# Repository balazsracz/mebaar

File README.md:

# Readme

This repository contains designs and files I made and collected for the Modelleisenbahn-Club Baar.

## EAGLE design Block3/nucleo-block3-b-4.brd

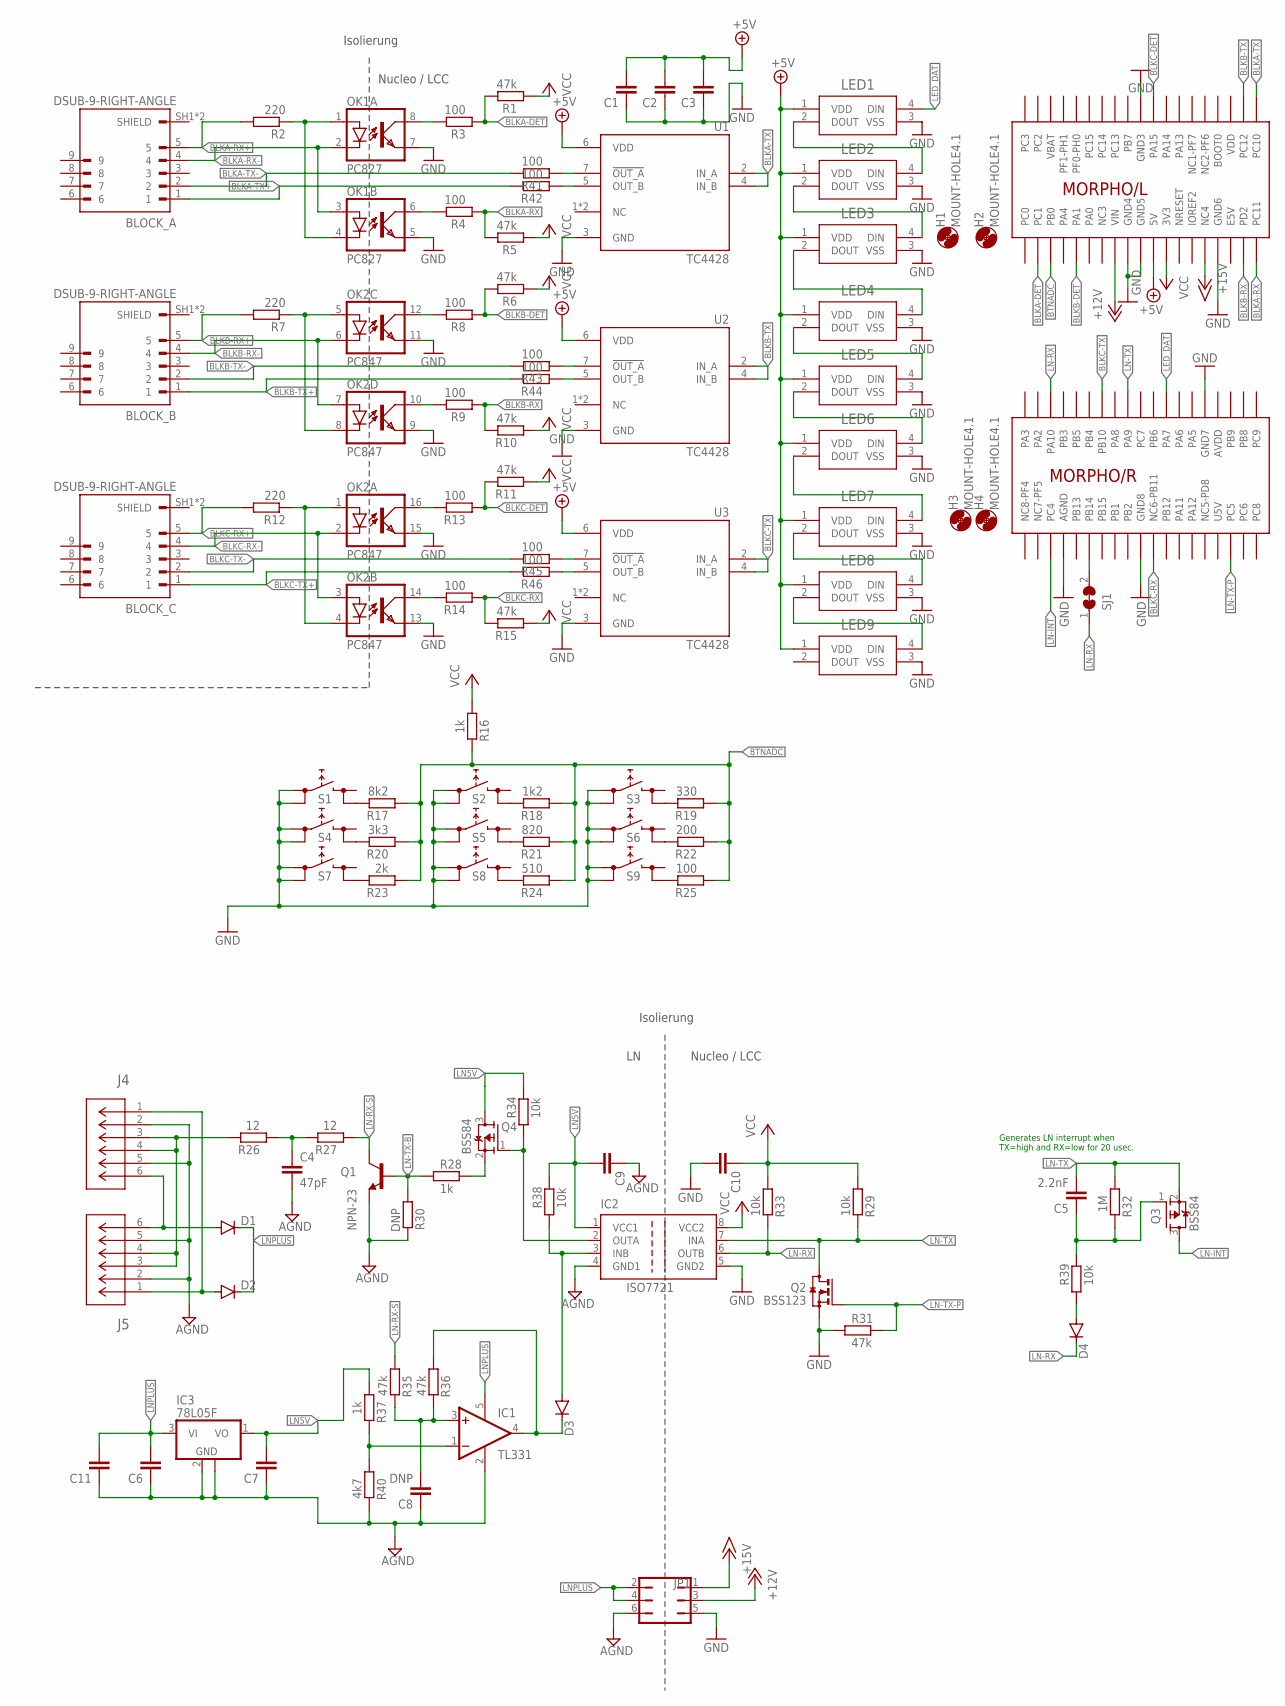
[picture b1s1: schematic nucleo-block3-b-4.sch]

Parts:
BLOCK_A: DSUB-9-RIGHT-ANGLE; ASSMANN_A-DS_09_A_KG-T2S
BLOCK_B: DSUB-9-RIGHT-ANGLE; ASSMANN_A-DS_09_A_KG-T2S
BLOCK_C: DSUB-9-RIGHT-ANGLE; ASSMANN_A-DS_09_A_KG-T2S
C1, C2, C3, C7: C-EUC0805; C0805
C4: 47pF; C0805
C5: 2.2nF; C0805
C6, C11: C-EUC0603K; C0603K
C8: DNP; C0603K
C9, C10: C-EUC0603; C0603
D1, D2: DIODE-DO214AA; DO214AA
D3, D4: DIODE-MINIMELF; MINIMELF
G1: NUCLEO_64_GENERIC; NUCLEO_BRD_BASE64
H1, H2, H3, H4: MOUNT-HOLE4.1; 4,1
IC1: TL331; DBV-R-PDSO-G5
IC2: ISO7721; SO-08
IC3: 78L05F; SOT89
J4, J5: MODJACK6P6C-MJ3245-66-0CONN_MJ3245-66-0_GCT; CONN_MJ3245-66-0_GCT
JP1: JP3Q
LED1, LED2, LED3, LED4, LED5, LED6, LED7, LED8, LED9: LED-2812BCOM-16347_SPK-M; COM-16347_SPK-M
OK1: PC827; DIL08
OK2: PC847; DIL16
Q1: NPN-23; SOT23
Q2: BSS123; SOT23-NCH
Q3, Q4: BSS84; SOT23-PCH
R1, R5, R6, R10, R11, R15, R31, R35, R36: 47k; R0805
R2, R7, R12: 220; R0805
R3, R4, R8, R9, R13, R14, R41, R42, R43, R44, R45, R46: 100; R0805
R16, R28, R37: 1k; R0805
R17: 8k2; R0603
R18: 1k2; R0603
R19: 330; R0603
R20: 3k3; R0603
R21: 820; R0603
R22: 200; R0603
R23: 2k; R0603
R24: 510; R0603
R25: 100; R0603
R26, R27: 12; R0805
R29, R33, R34, R38, R39: 10k; R0805
R30: DNP; R0805
R32: 1M; R0805
R40: 4k7; R0805
S1, S2, S3, S4, S5, S6, S7, S8, S9: W1; TACTSW-6X6
SJ1: SJ-C; SJW-C
U1, U2, U3: TC4428; SOIC127P600X175-8N

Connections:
+5V: C1.2, C2.2, C3.2, G1.5V2 (5V), LED1.1 (VDD), LED2.1 (VDD), LED3.1 (VDD), LED4.1 (VDD), LED5.1 (VDD), LED6.1 (VDD), LED7.1 (VDD), LED8.1 (VDD), LED9.1 (VDD), U1.6 (VDD), U2.6 (VDD), U3.6 (VDD)
+12V: G1.VIN2 (VIN), JP1.3
+15V: G1.NC4, JP1.1
AGND: C4.2, C6.1, C7.1, C8.1, C9.1, C11.1, IC1.2 (GND), IC2.4 (GND1), IC3.2 (GND), IC3.2@1 (GND), J4.2, J4.5, J5.2, J5.5, JP1.6, Q1.2 (E), R30.2, R40.2
AVDD: G1.AVDD
BLKA-DET: G1.PC1, R1.2, R3.1
BLKA-RX: G1.PC11, R4.1, R5.2
BLKA-RX+: BLOCK_A.5, R2.2
BLKA-RX-: BLOCK_A.4, OK1.2 (C), OK1.3 (A)
BLKA-TX: G1.PC10, U1.2 (IN_A), U1.4 (IN_B)
BLKA-TX+: BLOCK_A.1, R42.2
BLKA-TX-: BLOCK_A.2, R41.2
BLKB-DET: G1.PA1, R6.2, R8.1
BLKB-RX: G1.PD2, R9.1, R10.2
BLKB-RX+: BLOCK_B.5, R7.2
BLKB-RX-: BLOCK_B.4, OK2.6 (C), OK2.7 (A)
BLKB-TX: G1.PC12, U2.2 (IN_A), U2.4 (IN_B)
BLKB-TX+: BLOCK_B.1, R44.2
BLKB-TX-: BLOCK_B.2, R43.2
BLKC-DET: G1.PA15, R11.2, R13.1
BLKC-RX: G1.NC6-PB11, R14.1, R15.2
BLKC-RX+: BLOCK_C.5, R12.2
BLKC-RX-: BLOCK_C.4, OK2.2 (C), OK2.3 (A)
BLKC-TX: G1.PB10, U3.2 (IN_A), U3.4 (IN_B)
BLKC-TX+: BLOCK_C.1, R46.2
BLKC-TX-: BLOCK_C.2, R45.2
BTNADC: G1.PB0, R16.2, R17.1, R18.1, R19.1, R20.1, R21.1, R22.1, R23.1, R24.1, R25.1
E5V: G1.E5V
GND: C1.1, C2.1, C3.1, C10.2, G1.AGND, G1.GND3, G1.GND4, G1.GND5, G1.GND6, G1.GND7, G1.GND8, IC2.5 (GND2), JP1.5, LED1.3 (VSS), LED2.3 (VSS), LED3.3 (VSS), LED4.3 (VSS), LED5.3 (VSS), LED6.3 (VSS), LED7.3 (VSS), LED8.3 (VSS), LED9.3 (VSS), OK1.5 (EMIT), OK1.7 (EMIT), OK2.9 (EMIT), OK2.11 (EMIT), OK2.13 (EMIT), OK2.15 (EMIT), Q2.2 (S), R31.1, S1.1 (1.1), S1.2 (1.2), S2.1 (1.1), S2.2 (1.2), S3.1 (1.1), S3.2 (1.2), S4.1 (1.1), S4.2 (1.2), S5.1 (1.1), S5.2 (1.2), S6.1 (1.1), S6.2 (1.2), S7.1 (1.1), S7.2 (1.2), S8.1 (1.1), S8.2 (1.2), S9.1 (1.1), S9.2 (1.2), U1.3 (GND), U2.3 (GND), U3.3 (GND)
LED_DAT: G1.PA7, LED1.4 (DIN)
LN5V: C7.2, C9.2, IC2.1 (VCC1), IC3.1 (VO), Q4.3 (D), R34.2, R37.1, R38.2
LN-INT: G1.PC4, Q3.3 (D)
LN-RX: D4.C, G1.PA10, IC2.6 (OUTB), R33.2, SJ1.1
LN-RX-ALT: G1.PB14, SJ1.2
LN-RX-S: Q1.3 (C), R27.1, R35.1
LN-TX: C5.2, G1.PA9, IC2.7 (INA), Q2.3 (D), Q3.2 (S), R29.2, R32.1
LN-TX-B: Q1.1 (B), R28.1, R30.1
LN-TX-P: G1.PC5, Q2.1 (G), R31.2
LNPLUS: C6.2, C11.2, D1.C, D2.C, IC1.5 (V+), IC3.3 (VI), JP1.2, JP1.4
unnamed: OK2.1 (A), OK2.4 (C), R12.1
unnamed: OK2.16 (COL), R13.2
unnamed: OK2.14 (COL), R14.2
unnamed: D1.A, J4.6, J5.6
unnamed: C4.1, R26.1, R27.2
unnamed: D2.A, J4.1, J5.1
unnamed: J4.3, J4.4, J5.3, J5.4, R26.2
unnamed: IC2.2 (OUTA), Q4.1 (G), R34.1
unnamed: R17.2, S1.4 (2.2)
unnamed: D4.A, R39.1
unnamed: Q4.2 (S), R28.2
unnamed: LED1.2 (DOUT), LED2.4 (DIN)
unnamed: LED2.2 (DOUT), LED3.4 (DIN)
unnamed: LED3.2 (DOUT), LED4.4 (DIN)
unnamed: LED4.2 (DOUT), LED5.4 (DIN)
unnamed: LED5.2 (DOUT), LED6.4 (DIN)
unnamed: LED6.2 (DOUT), LED7.4 (DIN)
unnamed: LED7.2 (DOUT), LED8.4 (DIN)
unnamed: LED8.2 (DOUT), LED9.4 (DIN)
unnamed: D3.A, IC2.3 (INB), R38.1
unnamed: R20.2, S4.4 (2.2)
unnamed: C5.1, Q3.1 (G), R32.2, R39.2
unnamed: R23.2, S7.4 (2.2)
unnamed: R41.1, U1.7 (!OUT_A)
unnamed: R42.1, U1.5 (OUT_B)
unnamed: R18.2, S2.4 (2.2)
unnamed: R21.2, S5.4 (2.2)
unnamed: R24.2, S8.4 (2.2)
unnamed: IC1.1 (-IN), R37.2, R40.1
unnamed: C8.2, IC1.3 (+IN), R35.2, R36.2
unnamed: OK1.1 (A), OK1.4 (C), R2.1
unnamed: R19.2, S3.4 (2.2)
unnamed: R22.2, S6.4 (2.2)
unnamed: R25.2, S9.4 (2.2)
unnamed: OK2.5 (A), OK2.8 (C), R7.1
unnamed: D3.C, IC1.4 (OUT), R36.1
unnamed: R43.1, U2.7 (!OUT_A)
unnamed: R44.1, U2.5 (OUT_B)
unnamed: R45.1, U3.7 (!OUT_A)
unnamed: R46.1, U3.5 (OUT_B)
unnamed: OK1.8 (COL), R3.2
unnamed: OK1.6 (COL), R4.2
unnamed: OK2.12 (COL), R8.2
unnamed: OK2.10 (COL), R9.2
U5V: G1.U5V
VBAT: G1.VBAT
VCC: C10.1, G1.3V3, IC2.8 (VCC2), R1.1, R5.1, R6.1, R10.1, R11.1, R15.1, R16.1, R29.1, R33.1
VDD: G1.VDD

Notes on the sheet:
Isolierung
Nucleo / LCC
Generates LN interrupt when TX=high and RX=low for 20 usec.

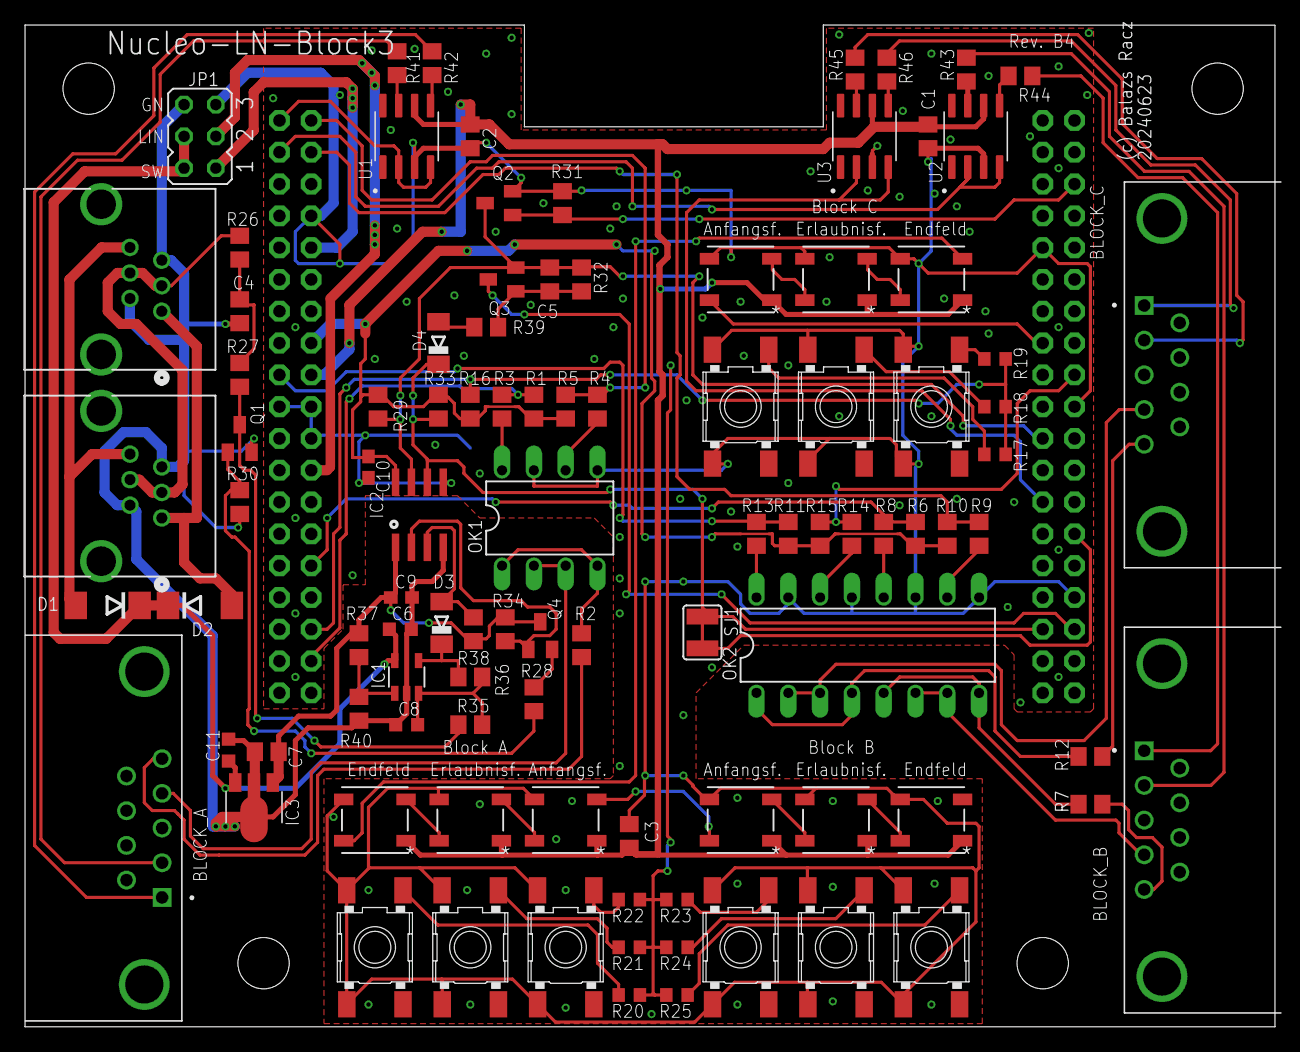
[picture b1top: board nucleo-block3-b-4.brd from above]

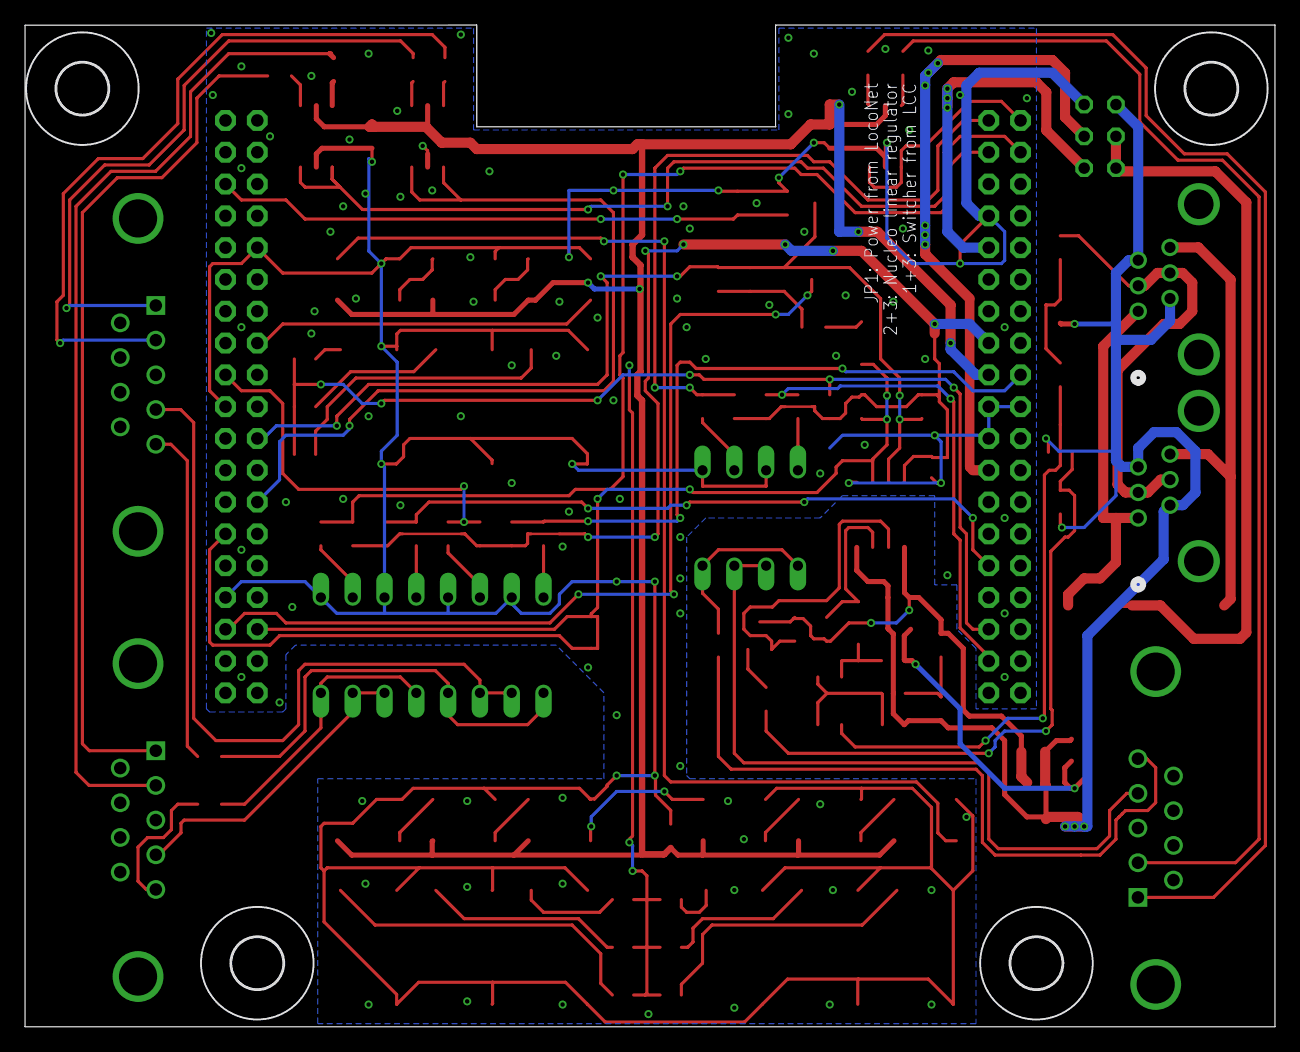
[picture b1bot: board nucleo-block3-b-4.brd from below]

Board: 2 copper layers, 99.8 x 80.0 mm, 103 parts (4 on the bottom side), 82 nets.

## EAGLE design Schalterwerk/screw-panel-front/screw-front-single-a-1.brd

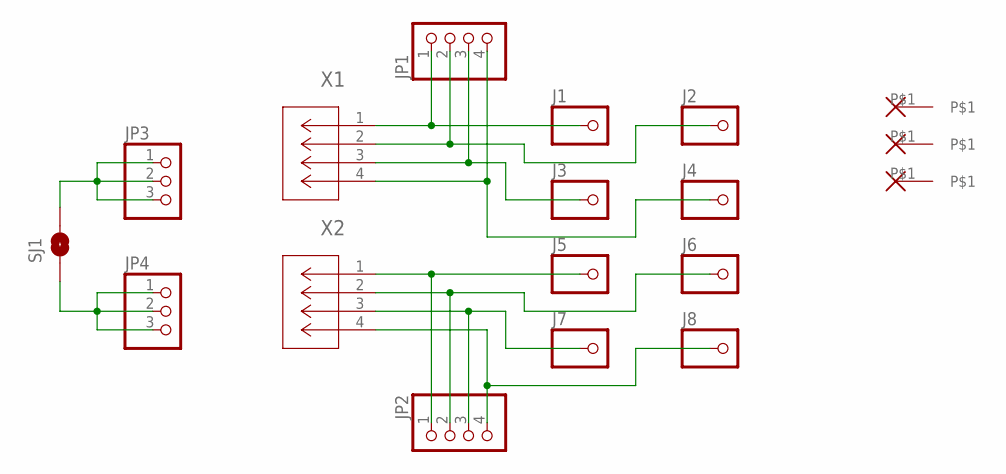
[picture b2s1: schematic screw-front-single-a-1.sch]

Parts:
H5, H6, H7: ALIGN-HOLE; ALIGNMENT-HOLE
J1, J2, J3, J4, J5, J6, J7, J8: M4-SCREW-HOLE
JP1, JP2: PINHD-1X4; 1X04
JP3, JP4: PINHD-1X3; 1X03
SJ1: SJRND2; SJ_RND2
X1, X2: PHNX_4P_350CONN_1984989_PXC; PHNX_4P_350

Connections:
unnamed: J1.P$1, JP1.1, X1.1
unnamed: J2.P$1, JP1.2, X1.2
unnamed: J3.P$1, JP1.3, X1.3
unnamed: J4.P$1, JP1.4, X1.4
unnamed: J5.P$1, JP2.1, X2.1
unnamed: J6.P$1, JP2.2, X2.2
unnamed: J7.P$1, JP2.3, X2.3
unnamed: J8.P$1, JP2.4, X2.4
unnamed: JP3.1, JP3.2, JP3.3, SJ1.P$2 (2)
unnamed: JP4.1, JP4.2, JP4.3, SJ1.P$1 (1)

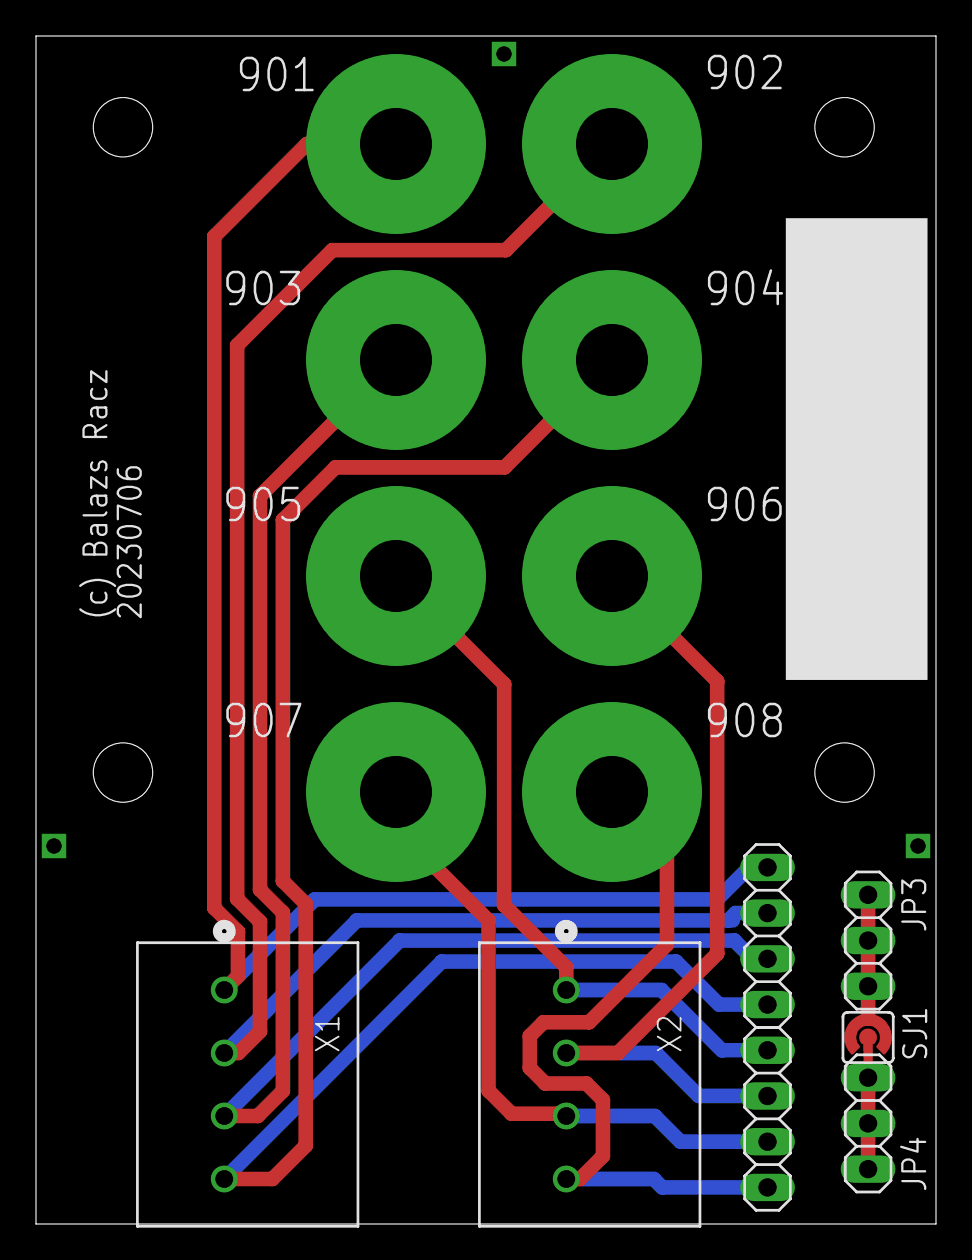
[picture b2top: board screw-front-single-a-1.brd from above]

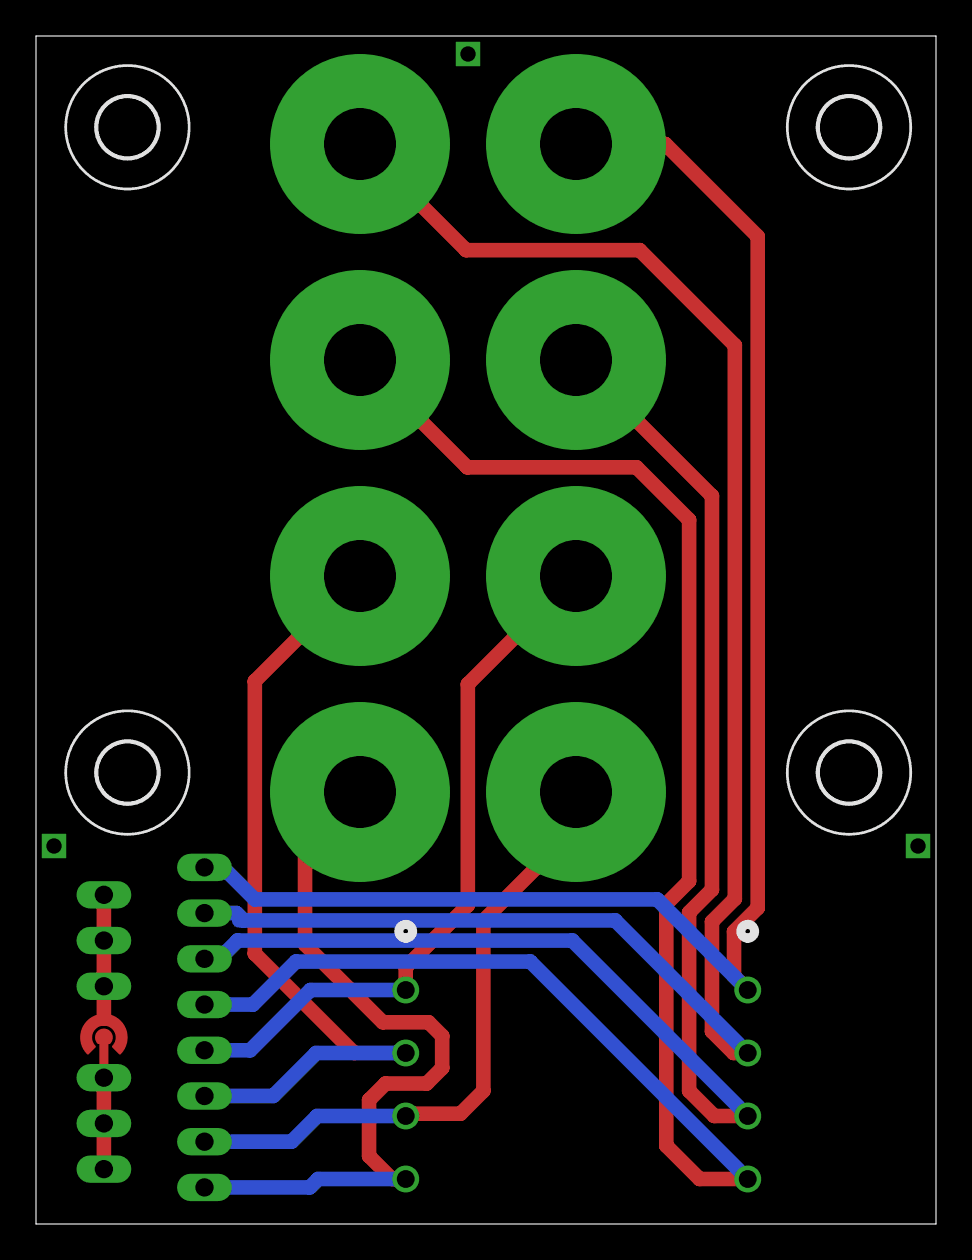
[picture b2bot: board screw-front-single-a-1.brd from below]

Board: 2 copper layers, 50.0 x 66.0 mm, 22 parts (4 on the bottom side), 10 nets.

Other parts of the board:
H1, H2, H3, H4: MOUNT-HOLE3.3; 3,3

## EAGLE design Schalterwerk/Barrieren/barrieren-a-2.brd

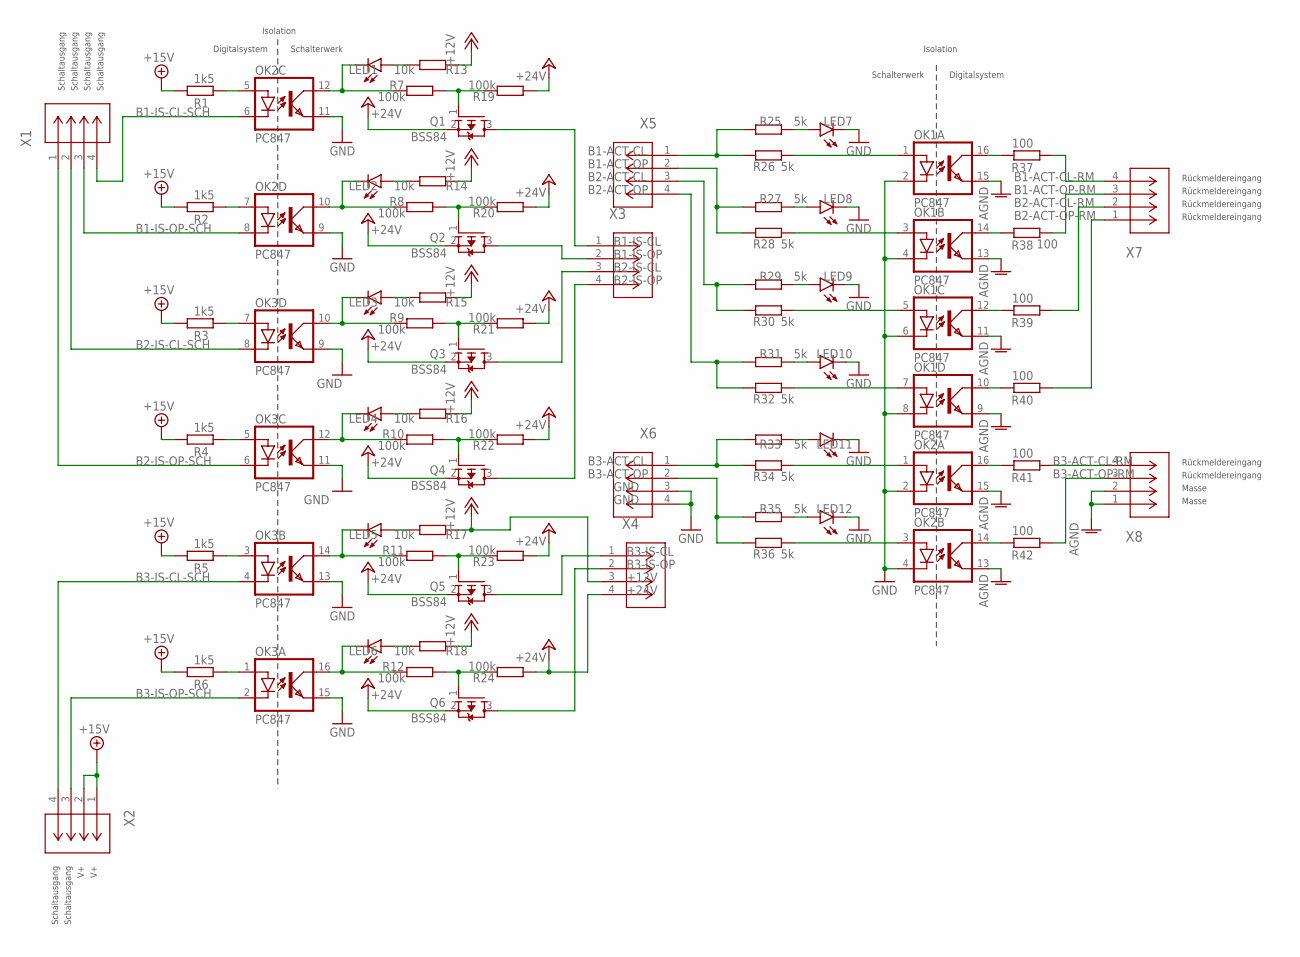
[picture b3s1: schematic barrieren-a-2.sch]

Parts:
LED1, LED2, LED3, LED4, LED5, LED6, LED7, LED8, LED9, LED10, LED11, LED12: LEDCHIPLED_0603; CHIPLED_0603
OK1, OK2, OK3: PC847; DIL16
Q1, Q2, Q3, Q4, Q5, Q6: BSS84; SOT23-PCH
R1, R2, R3, R4, R5, R6: 1k5; R0805
R7, R8, R9, R10, R11, R12, R19, R20, R21, R22, R23, R24: 100k; R0805
R13, R14, R15, R16, R17, R18: 10k; R0805
R25, R26, R27, R28, R29, R30, R31, R32, R33, R34, R35, R36: 5k; R0805
R37, R38, R39, R40, R41, R42: 100; R0805
X1, X2, X3, X4, X5, X6, X7, X8: PHNX_4P_350CONN_1984989_PXC; PHNX_4P_350

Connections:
+12V: R13.2, R14.2, R15.2, R16.2, R17.2, R18.2, X4.3
+15V: R1.1, R2.1, R3.1, R4.1, R5.1, R6.1, X2.1, X2.2
+24V: Q1.2 (S), Q2.2 (S), Q3.2 (S), Q4.2 (S), Q5.2 (S), Q6.2 (S), R19.2, R20.2, R21.2, R22.2, R23.2, R24.2, X4.4
AGND: OK1.9 (EMIT), OK1.11 (EMIT), OK1.13 (EMIT), OK1.15 (EMIT), OK2.13 (EMIT), OK2.15 (EMIT), X8.1, X8.2
B1-ACT-CL: R25.2, R26.2, X5.1
B1-ACT-CL-RM: R37.1, X7.4
B1-ACT-OP: R27.2, R28.2, X5.2
B1-ACT-OP-RM: R38.1, X7.3
B1-IS-CL: Q1.3 (D), X3.1
B1-IS-CL-SCH: OK2.6 (C), X1.4
B1-IS-OP: Q2.3 (D), X3.2
B1-IS-OP-SCH: OK2.8 (C), X1.3
B2-ACT-CL: R29.2, R30.2, X5.3
B2-ACT-CL-RM: R39.1, X7.2
B2-ACT-OP: R31.2, R32.2, X5.4
B2-ACT-OP-RM: R40.1, X7.1
B2-IS-CL: Q3.3 (D), X3.3
B2-IS-CL-SCH: OK3.8 (C), X1.2
B2-IS-OP: Q4.3 (D), X3.4
B2-IS-OP-SCH: OK3.6 (C), X1.1
B3-ACT-CL: R33.2, R34.2, X6.1
B3-ACT-CL-RM: R41.1, X8.4
B3-ACT-OP: R35.2, R36.2, X6.2
B3-ACT-OP-RM: R42.1, X8.3
B3-IS-CL: Q5.3 (D), X4.1
B3-IS-CL-SCH: OK3.4 (C), X2.4
B3-IS-OP: Q6.3 (D), X4.2
B3-IS-OP-SCH: OK3.2 (C), X2.3
GND: LED7.C, LED8.C, LED9.C, LED10.C, LED11.C, LED12.C, OK1.2 (C), OK1.4 (C), OK1.6 (C), OK1.8 (C), OK2.2 (C), OK2.4 (C), OK2.9 (EMIT), OK2.11 (EMIT), OK3.9 (EMIT), OK3.11 (EMIT), OK3.13 (EMIT), OK3.15 (EMIT), X6.3, X6.4
unnamed: Q1.1 (G), R7.1, R19.1
unnamed: OK2.1 (A), R34.1
unnamed: LED12.A, R35.1
unnamed: LED11.A, R33.1
unnamed: OK2.5 (A), R1.2
unnamed: OK1.12 (COL), R39.2
unnamed: OK2.3 (A), R36.1
unnamed: OK2.7 (A), R2.2
unnamed: OK1.10 (COL), R40.2
unnamed: OK1.5 (A), R30.1
unnamed: LED1.A, R13.1
unnamed: LED2.A, R14.1
unnamed: LED2.C, OK2.10 (COL), R8.2
unnamed: Q2.1 (G), R8.1, R20.1
unnamed: OK3.7 (A), R3.2
unnamed: OK1.7 (A), R32.1
unnamed: LED9.A, R29.1
unnamed: LED3.A, R15.1
unnamed: OK2.16 (COL), R41.2
unnamed: LED3.C, OK3.10 (COL), R9.2
unnamed: OK2.14 (COL), R42.2
unnamed: Q3.1 (G), R9.1, R21.1
unnamed: OK3.5 (A), R4.2
unnamed: LED10.A, R31.1
unnamed: LED4.A, R16.1
unnamed: OK1.16 (COL), R37.2
unnamed: LED1.C, OK2.12 (COL), R7.2
unnamed: OK1.14 (COL), R38.2
unnamed: OK1.1 (A), R26.1
unnamed: LED4.C, OK3.12 (COL), R10.2
unnamed: OK1.3 (A), R28.1
unnamed: LED7.A, R25.1
unnamed: LED8.A, R27.1
unnamed: Q4.1 (G), R10.1, R22.1
unnamed: OK3.3 (A), R5.2
unnamed: LED5.A, R17.1
unnamed: LED5.C, OK3.14 (COL), R11.2
unnamed: Q5.1 (G), R11.1, R23.1
unnamed: OK3.1 (A), R6.2
unnamed: LED6.A, R18.1
unnamed: LED6.C, OK3.16 (COL), R12.2
unnamed: Q6.1 (G), R12.1, R24.1

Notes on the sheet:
Rückmeldereingang
Masse
Schaltausgang
Isolation
Schalterwerk
Digitalsystem

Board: 2 copper layers, 75 parts (4 on the bottom side), 71 nets, no tracks yet.

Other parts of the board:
H1, H2, H3, H4: MOUNT-HOLE3.3; 3,3

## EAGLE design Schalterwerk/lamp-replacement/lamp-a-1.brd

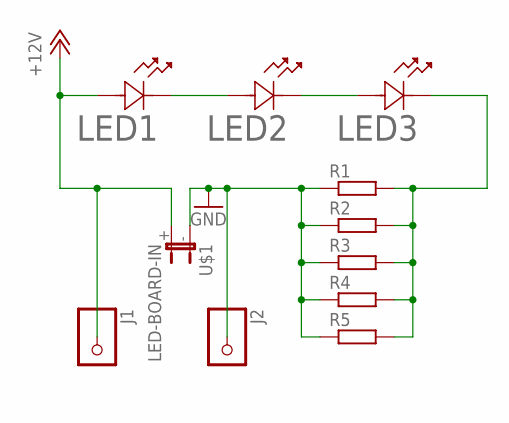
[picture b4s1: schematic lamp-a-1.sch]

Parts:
J1, J2: LARGE-SOLDERPAD
LED1, LED2, LED3: LED-2835LED_J2835_CRW-M; LED_J2835_CRW-M
R1, R2, R3, R4, R5: R-EU_R0805; R0805
U$1: LED-BOARD-IN

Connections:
+12V: J1.P$1, LED1.2, U$1.+ (2)
GND: J2.P$1, R1.1, R2.1, R3.1, R4.1, R5.1, U$1.- (1)
unnamed: LED1.1, LED2.2
unnamed: LED2.1, LED3.2
unnamed: LED3.1, R1.2, R2.2, R3.2, R4.2, R5.2

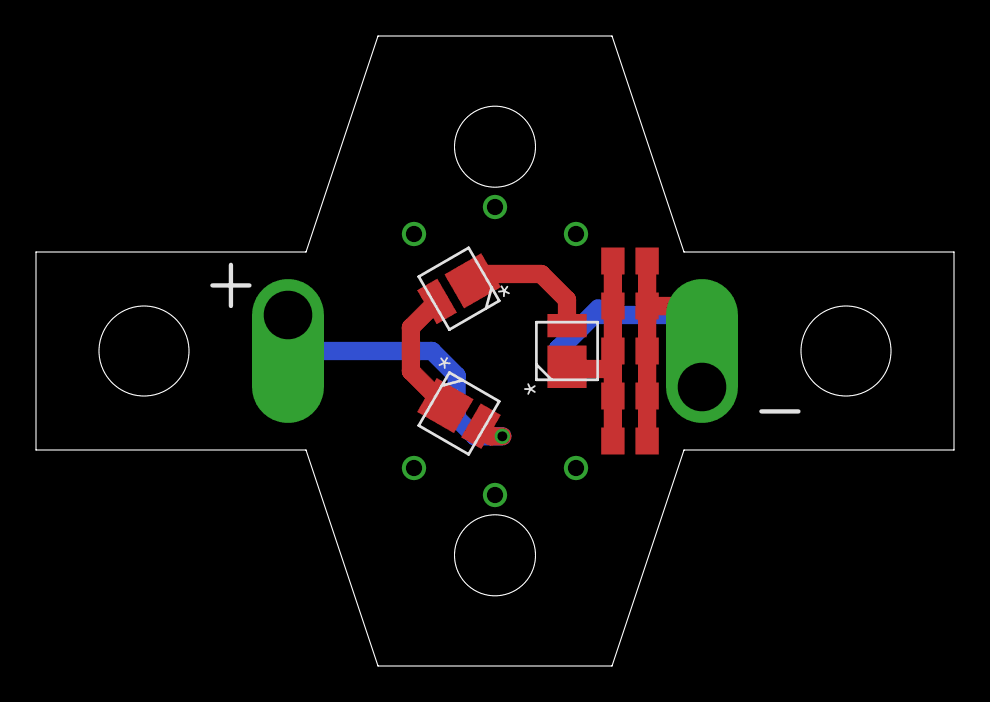
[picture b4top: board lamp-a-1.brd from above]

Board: 2 copper layers, 51.0 x 35.0 mm, 11 parts (1 on the bottom side), 5 nets.

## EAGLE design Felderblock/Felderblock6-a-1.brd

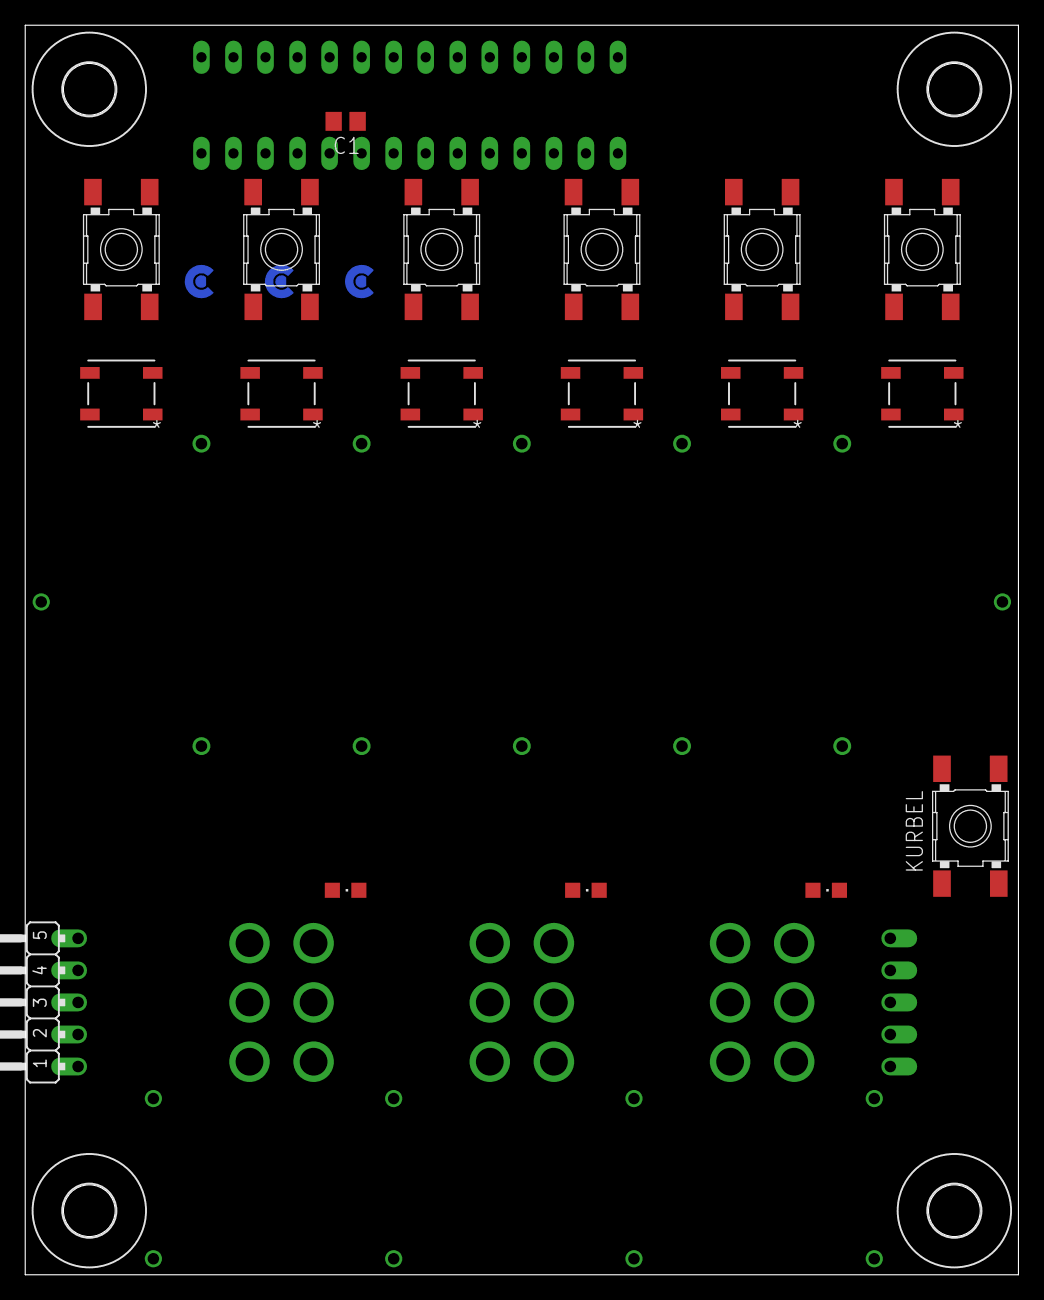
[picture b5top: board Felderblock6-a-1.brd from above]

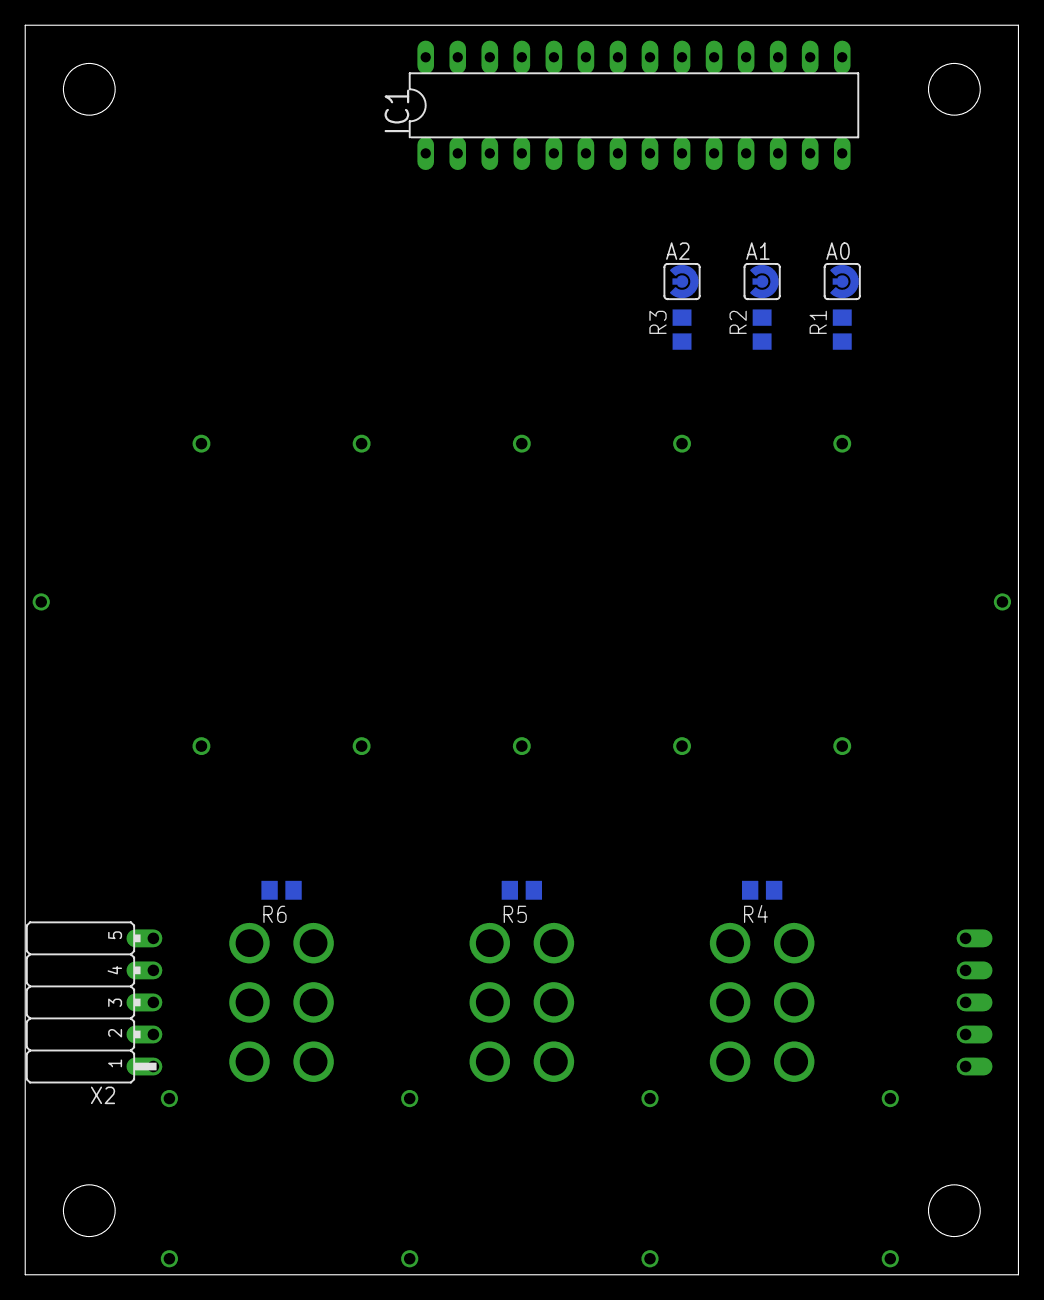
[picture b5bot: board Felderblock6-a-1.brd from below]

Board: 2 copper layers, 78.7 x 99.1 mm, 41 parts (11 on the bottom side), 33 nets, no tracks yet.

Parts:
A0, A1, A2: SJ_RND2
C1: C0805
H1, H2, H3, H4: MOUNT-HOLE4.1; 4,1
IC1: MCP23017SP; DIL28-3
JP1, JP2, JP3, JP4, JP5: FELD-BOARD-HOLDER
KURBEL: W1; TACTSW-6X6
LED1, LED2, LED3, LED4, LED5, LED6: COM-16347_SPK-M
LED7, LED8, LED9: CHIPLED_0805
R1, R2, R3: 47k; R0805
R4, R5, R6: 330; R0805
S1, S2, S3, S4, S5, S6: W1; TACTSW-6X6
S8, S9, S10: DP-T1
X1: JP5-FLAT; JP5F
X2: JP5-FLATFEMALE; JP5F-FEM

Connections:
+5V: C1.1, IC1.9, IC1.18, LED1.1, LED2.1, LED3.1, LED4.1, LED5.1, LED6.1, R1.1, R2.1, R3.1, X1.3, X2.3
GND: A0.P$1, A1.P$1, A2.P$1, C1.2, IC1.10, KURBEL.1, KURBEL.2, LED1.3, LED2.3, LED3.3, LED4.3, LED5.3, LED6.3, LED7.C, LED8.C, LED9.C, S1.1, S1.2, S2.1, S2.2, S3.1, S3.2, S4.1, S4.2, S5.1, S5.2, S6.1, S6.2, S8.2, S9.2, S10.2, X1.4, X2.4
I2CSCL: IC1.12, X1.1, X2.1
I2CSDA: IC1.13, X1.2, X2.2
LEDF1: IC1.27, R4.1
LEDF2: IC1.28, R5.1
LEDF3: IC1.1, R6.1
LED_DAT: LED1.4, X1.5
LED_OUT: LED6.2, X2.5
unnamed: A0.P$2, IC1.15, R1.2
unnamed: A1.P$2, IC1.16, R2.2
unnamed: A2.P$2, IC1.17, R3.2
unnamed: IC1.21, S1.4
unnamed: IC1.22, S2.4
unnamed: IC1.23, S3.4
unnamed: IC1.24, S4.4
unnamed: IC1.25, S5.4
unnamed: IC1.26, S6.4
unnamed: IC1.8, S8.1
unnamed: IC1.7, S8.3
unnamed: LED1.2, LED2.4
unnamed: LED2.2, LED3.4
unnamed: LED3.2, LED4.4
unnamed: LED4.2, LED5.4
unnamed: LED5.2, LED6.4
unnamed: IC1.6, S9.1
unnamed: IC1.5, S9.3
unnamed: IC1.4, S10.1
unnamed: IC1.3, S10.3
unnamed: LED8.A, R5.2
unnamed: LED7.A, R4.2
unnamed: LED9.A, R6.2
unnamed: IC1.2, KURBEL.4

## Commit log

2023-04-07 Adds README and LICENSE files
2023-04-07 Adds schematic of the fuse rev. A.
2023-04-07 Ignores eagle backup save files.
2023-04-08 Adds LED to show fault. Moves the emitter of the darlington stage tothe collector of the main stage. This will prevent too high base voltage when the PTC is tripped.
2023-04-08 Updates transistor symbol. Updates package to DPAK. Adds PTC. Adds solder jumpers.
2023-04-08 Adds mounting holes as placeholders for terminals.
2023-04-08 Adds protection diode to prevent the base of Q1 to be too much above the emitter.
2023-04-08 Adds tip connectors to the schematic and to the library. Places components on the board.
2023-04-08 Completes routing signals. Adjusts silkscreen.
2023-04-09 Adds another 4mm banana jack to cover for the case where two 4mm pins are 28mm away from each other. This makes this single design capable of subbing for three out of four different types of fuses.
2023-04-09 Adds some datasheets and the CAM file for pcbway.
2023-04-09 Adds a bunch of vias into the banana plug footprint. Updates the outline. Adds (c) line and date.
2023-04-09 Submitted gerber files.
2023-04-10 Adds a blade slotted plug to the library.
2023-04-10 Adds reference drawing of the AMP connector we can put in as a blade.
2023-04-10 Adds alternative schematic and board file with the blade type plugs.
2023-04-10 Adds a documentation rectangle to show where the hole is going to be.
2023-04-10 Completes the layout of the fuse with blade inputs.
2023-04-10 Adds eagle description file.
2023-05-13 Adds newer versions of the Sicherung.
2023-05-13 Adds gerbers that were sent for ordering devices.
2023-05-13 Updates opening for the blade connector to be tighter with less tolerance.
2023-05-13 Adds pdf versions of the schematic.
2023-05-13 Cleanup.
2023-05-14 Adds first version of gleisbelegtmelder.
2023-05-18 Adds pdf rendering of the circuit.
2023-05-18 Updates the solder jumpers to connect neighboring traces on the bus side.
2023-05-18 Adds library component for IO-daughterboard-socket.
2023-05-18 Adds schematic for IO daughterboard.
2023-05-18 Completes board layout and routing for the daughterboard.
2023-05-19 Adds weichenschaltung and signalschaltung.
2023-05-21 Updates the frames on the schematics with proper project information.
    Adds LEDs for observing what is happening on the Gleisbelegtmeldung.
2023-05-21 Adds library for an external LED via header. Adds library component for the IO daughterboard.
2023-05-21 Updates board size to match grid.
2023-05-21 Adds LED.
2023-05-21 Adds component layout to the board. Routes the isolated part of the traces.
2023-05-21 Finishes routing and adds ground pour.
2023-05-22 Compresses the space needed for the male and female connection headers.
    Adds molex picoblade connectors.
2023-05-22 Adds molex picoblade connectors as alternative for uplink/dnlink.
    Finishes layout with labels and text.
2023-05-22 Updates the footprint of the daughterboard.
2023-05-22 Adds ground pour and connecting GND vias. Adds thermal-less poly under the regulator.
2023-05-29 Updates layout of the io daughterboard. Updates silkscreen documentation.
2023-05-29 Adds second version of the io daughterboard. Adds gerbers.
2023-05-29 Adds triangle for pin 1 of the io daughterboard profile.
2023-05-29 Finalizes first version of the gleisbelegung board. Adds gerbers.
2023-05-29 Closes out first release of Weichenschaltung.
2023-05-29 Adds an alternative CAM processor definition which prints tvalue / tplace / tname on the silkscreen. Some of the devices in out libraries rely on these all appearing on the silk.
2023-05-29 Adds second version of weichenschaltung, where we assume a simplified wiring on the stellwerk side.
2023-05-29 Removes not-laid-out weichenschaltung file.
2023-05-29 Adds default generated layout.
2023-05-29 Renumbers the schematic so that the digitalsystem side can be copy-pasted between layouts.
2023-05-29 Renames signals on X4 again
2023-05-29 Completes copy-paste of the layout of the conneectors to the schalterwerk.
2023-05-30 Does much of the board layout. Switches the pins on the connector to the schalterwerk so that it is in the order of L1 .. L4.
2023-06-01 Adds version 3 gleisfreimeldung files.
2023-06-03 Adds all display LEDs, completes layout.
2023-06-03 Adds ports to connect adjacent boards. Adds ground pour.
2023-06-03 Fixes layer of name labels (it was on the value layer).
2023-06-03 Adds Weichenadapter v4.
2023-06-03 Updates rev number to A4.
2023-06-03 Fixes issues found on the gerbers.
2023-06-03 Adds a board design outline for the signal adapter.
2023-06-04 Adds rev A5 of the weichenschaltung. Fixes the grid of the side connectors from 2 mm to 100 mil
2023-06-04 Adds a 5-position connector on the side with offset solder pads.
2023-06-04 Adds the side pinheader with 6 pins.
2023-06-04 Finishes layout of signal adapter. Adds side connector for IO.
2023-06-04 Adds submitted gerbers file for signal.
2023-06-05 Adds a simple board to take four sicherungen with sockets.
2023-06-05 Adds part for taking in a sicherung (socket). Adds part for soldering a large gauge wire to the edge of a board.
2023-06-17 Updates incorrect or inconsistent resistor values.
2023-06-17 Adds resistor networks.
2023-06-17 Adds rendered schematics.
2023-06-17 Adds more datasheets to the reference library.
2023-06-20 Adds Weichen version 6 board gerbers. Adds PDF for signal a-2
2023-06-20 Adds update to Weichenschaltung, specifically to make the board wider and avoid the mechanical conflict on the input panel.
2023-06-20 Adds incomplete version of the mini input board.
2023-06-25 Fixes instructions on the weichen rework.
2023-06-25 Completes design for the Lampen input board.
2023-06-26 Resizes pads on the 8-resistor SMD network for pullup.
2023-06-26 Updates pad layout of 8-resistor pullup network.
2023-06-26 Make text shorter. Adds gerber files.
2023-06-26 Adds a first version of the screw panel mounting board.
2023-07-06 Adds single-back screw panel with gerbers.
2023-07-06 Adds alternate package for screw head.
2023-07-06 Forks design for single screw front panel.
2023-07-08 Adds gerbers of boards that were ordered.
2024-03-17 Updates page titles.
2024-03-17 Adds PDFs for mini input.
2024-03-17 Save files temporarily
2024-03-17 Rename screw front to screw-front-double.
2024-03-28 misc updates
2024-03-28 Adds initial sketch of the dual relay board.
2024-03-30 Adds name and label to the footprint for large solderpad.
2024-03-30 Adds values to the large solderpads that explain what should be connected.
2024-03-30 Adds slimmer circuit with fewer input pads and fewer solder jumpers. Forks it for routing.
2024-03-30 Finishes routing of the turnout relay board.
2024-03-30 Adds some labels to make the IN/OUT more understandable. Renames some nets for the labels.
2024-03-30 Adds P-channel SOT23 mosfet.
2024-03-30 Adds schematic for temporary stellwerk.
2024-03-31 Updates some of the values of the parts.
2024-03-31 Creates board and lays out the user interface parts.
2024-03-31 Updates names of all buttons.
2024-03-31 Lays out all SMD parts on the bottom side.
2024-03-31 Adds copy of design, sets net class to 10 mil.
2024-03-31 adds clearance requirement for net 0
2024-03-31 autorouter settings
2024-03-31 Adds autorouted version of the design.
2024-03-31 Makes a visual difference between n-ch and p-ch SOT23 transistors.
2024-04-01 Adds ground planes and vias between ground planes.
2024-04-01 Adds gerbers that were ordered.
2024-04-29 Adds schematic files for a triple fremo-block interface.
2024-04-29 Adds morpho header. Lays out connectors.
2024-04-29 Adds LN circuitry.
2024-04-29 Adds addressable LED library.
2024-04-29 Adds addressable LEDs.
2024-04-29 Places the jacks.
2024-04-29 Replace 6p6c jack with a different one that is smaller in size.
2024-04-30 Adds (broken) rev 2 schematic
2024-04-30 Adds rev 3 schematic and board.
2024-04-30 Adds loconet interrupt circuit. Links more things to the nucleo.
2024-04-30 Adds analog read-in buttons.
2024-05-02 Adds mount hole alternative package with a laser cut hole.
2024-05-02 Adds laser cut board layout
2024-05-02 Adds circles to laser around the tactile buttons.
2024-05-02 Adds laser holes on top of the LEDs.
2024-05-02 Adds first pass laser printout in dxf and pdf.
2024-05-02 Adds v4 laser ready schematic.
2024-05-03 Updates text locations and adds some more text for turnouts.
2024-05-03 Adds all turnout button labels and Fdl location.
2024-05-03 Adds final versions of lasered overlays.
2024-05-03 Adds routing of the loconet input voltage to an NC pin to drive the 5V switcher. Adds a comparator based loconet input voltage decoder. Finishes the button grid.
2024-05-03 Adds rev A4. Makes an isolated loconet receiver circuit.
2024-05-03 rearranges schematic sheets.
2024-05-03 Rearranges gates of the optocouplers.
2024-05-03 Removes the ground planes for now.
2024-05-05 Arranges the optocouplers.
2024-05-05 Renumbers parts.
2024-05-05 Routing the board.
2024-05-05 Adds final routed board.
2024-05-08 Adds schematic for 6-way Felderblock.
2024-05-08 Adds gerber files ordered.
2024-05-08 Adds completed board and autorouted version.
2024-06-01 Adds labels for IO port.
2024-06-01 Adds 2835 LED device.
2024-06-01 Adds fork to start modifying for a second run.
2024-06-01 Adds lamp replacement board design.
2024-06-01 Finishes layout of the lamp circuit.
2024-06-01 Removes unnecessary clutter from 2835 LED.
2024-06-01 adds supports for vertical pipe.
2024-06-01 Renames sch/brd to have version numbers.
2024-06-01 removes +- labels from the bottom.
2024-06-01 Adds first cut of schematic ofr barrierenschaltung.
2024-06-01 Places connectors and adds labeling.
2024-06-04 Adds second rev.
2024-06-07 Continue on layout of barrieren board.
2024-06-07 Updates font and size of labels.
2024-06-07 Finishes placing the components.
2024-06-07 Rev a3 for barrieren schematic.
2024-06-07 Routes the airwires
2024-06-07 removes unneeded mounting hole.
2024-06-09 Final tweaks to board. Adds ground planes and vias. Label tweaks.
2024-06-09 Adds rendered schematic and gerbers files.
2024-06-23 - adds a small TH pin "alignment hole" to the lib - fixes the DB-9 connector's pin order - updates the loconet-block3 board for rev B.
2024-06-23 Adds alignment holes.
2024-06-29 Final brd/sch that was ordered.
2024-06-29 Adds gerbers that were sent for production.
2025-03-23 Ignores generated gerber files.
2025-03-23 Adds single-column front panels that were ordered for the schalterwerk.
2025-03-23 Adds easyeda schematics and board file for rev.0 of the SPI I/O board for hebelstellwerke.
2025-03-23 Updates 12V track to run on the left side.

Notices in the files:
Block3/nucleo-block3-b-4.sch:
LICENSE: Licensed by the Solderpad Hardware License V2.0
parts and their libraries:
COPYRIGHT: Copyright (C) 2024 Ultra Librarian. All rights reserved.
COPYRIGHT: Copyright (C) 2023 Ultra Librarian. All rights reserved.
